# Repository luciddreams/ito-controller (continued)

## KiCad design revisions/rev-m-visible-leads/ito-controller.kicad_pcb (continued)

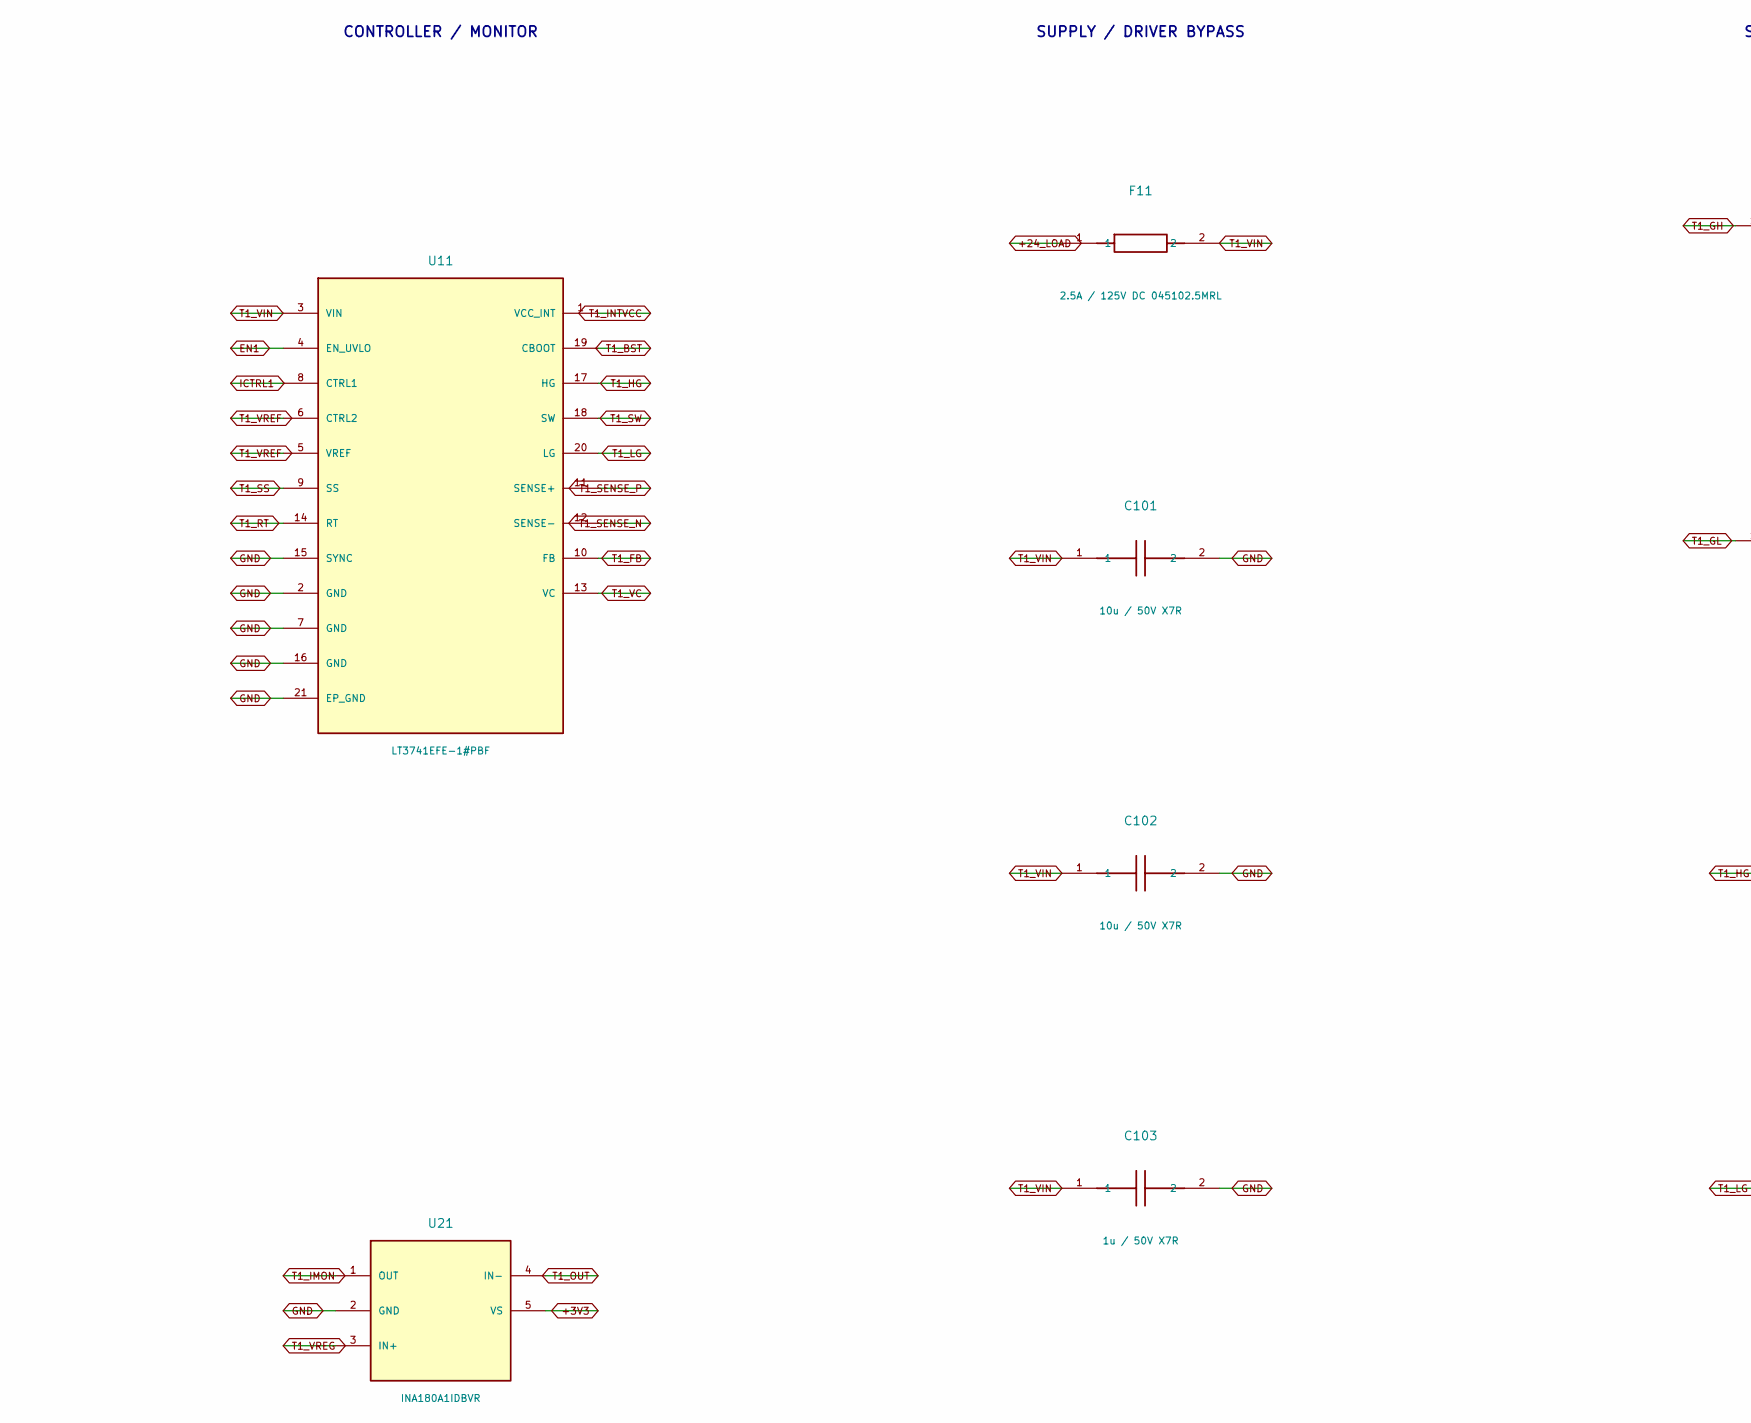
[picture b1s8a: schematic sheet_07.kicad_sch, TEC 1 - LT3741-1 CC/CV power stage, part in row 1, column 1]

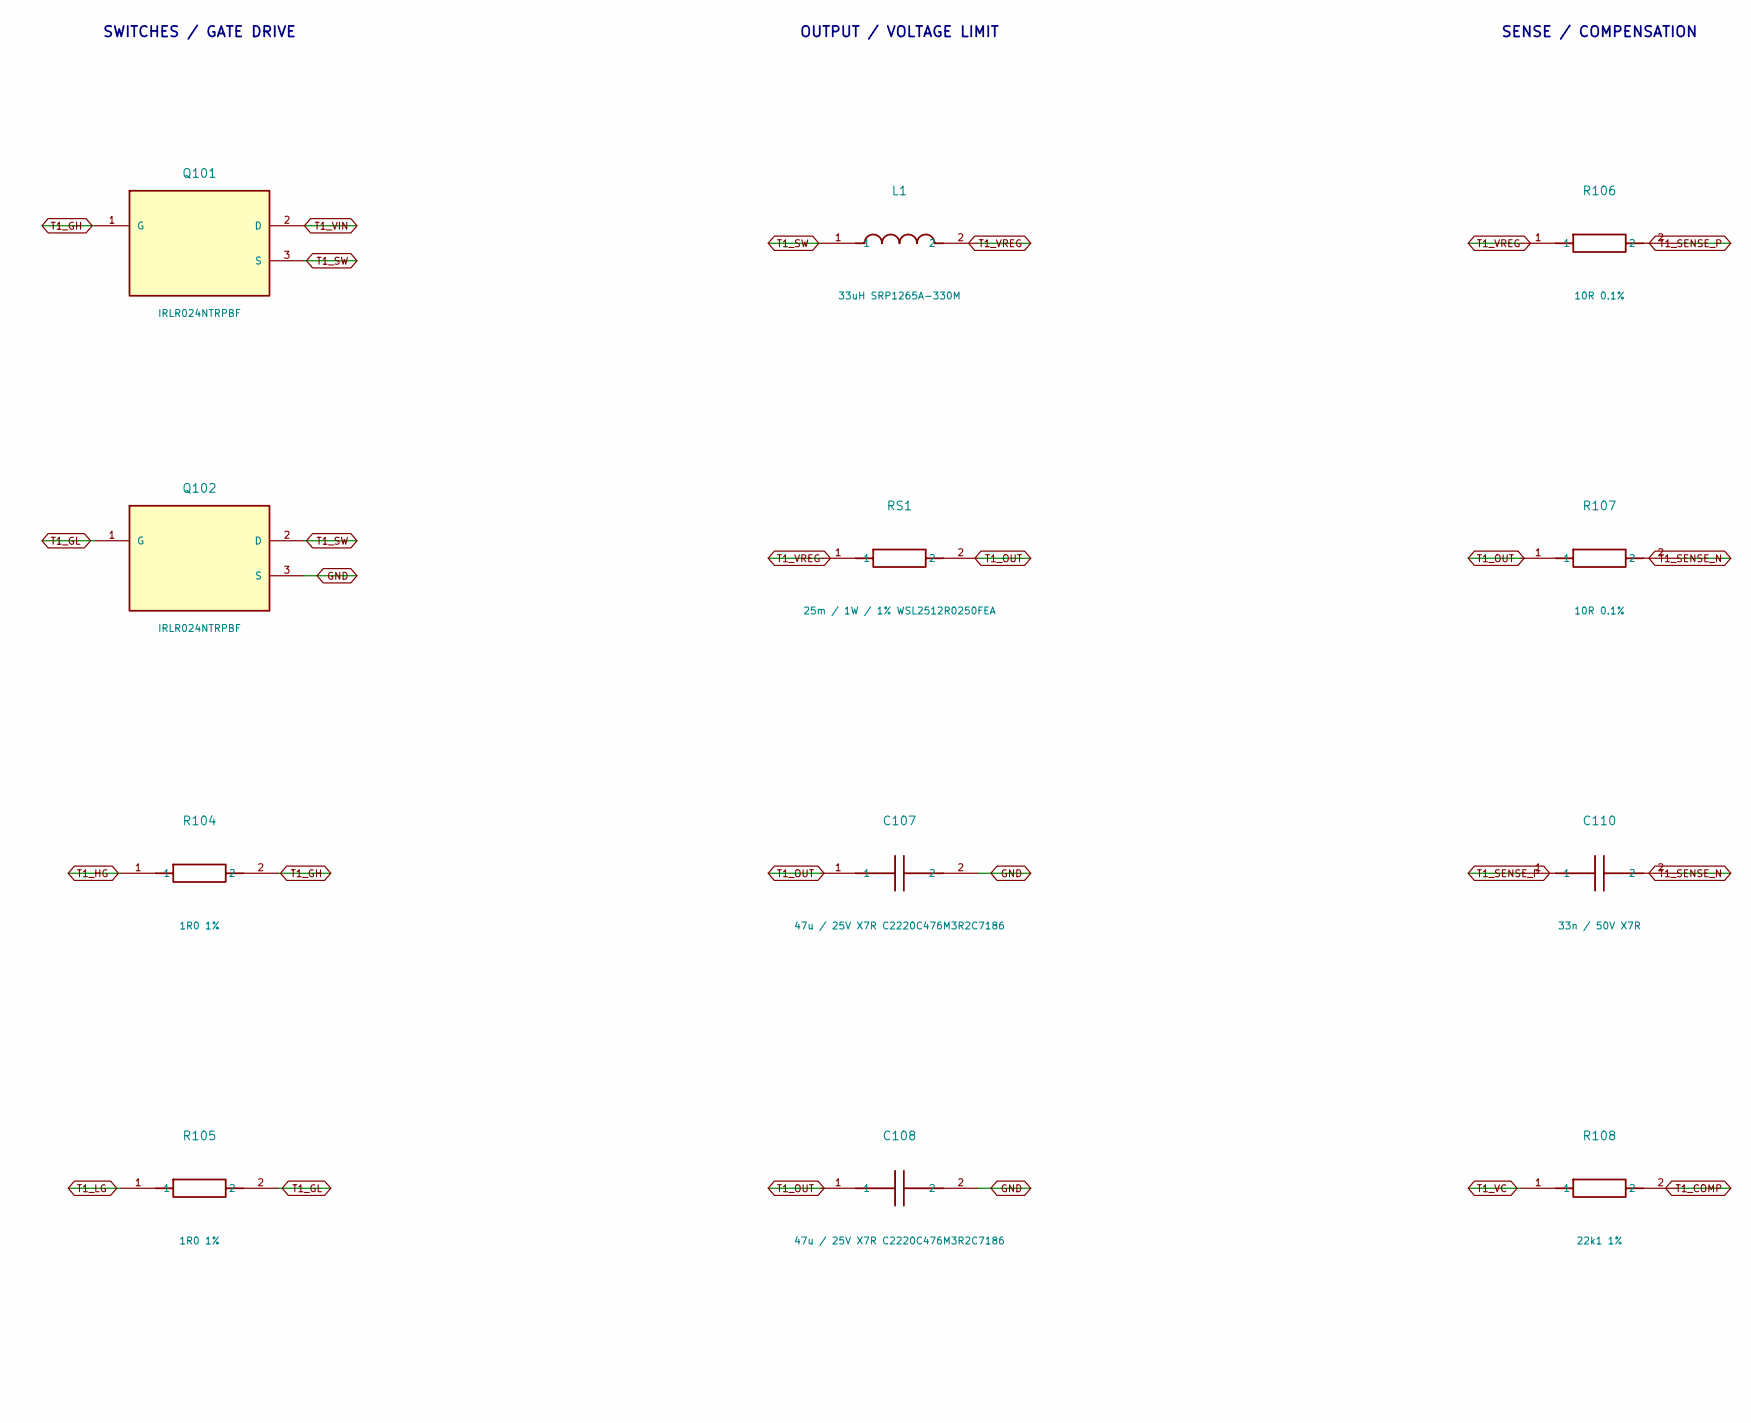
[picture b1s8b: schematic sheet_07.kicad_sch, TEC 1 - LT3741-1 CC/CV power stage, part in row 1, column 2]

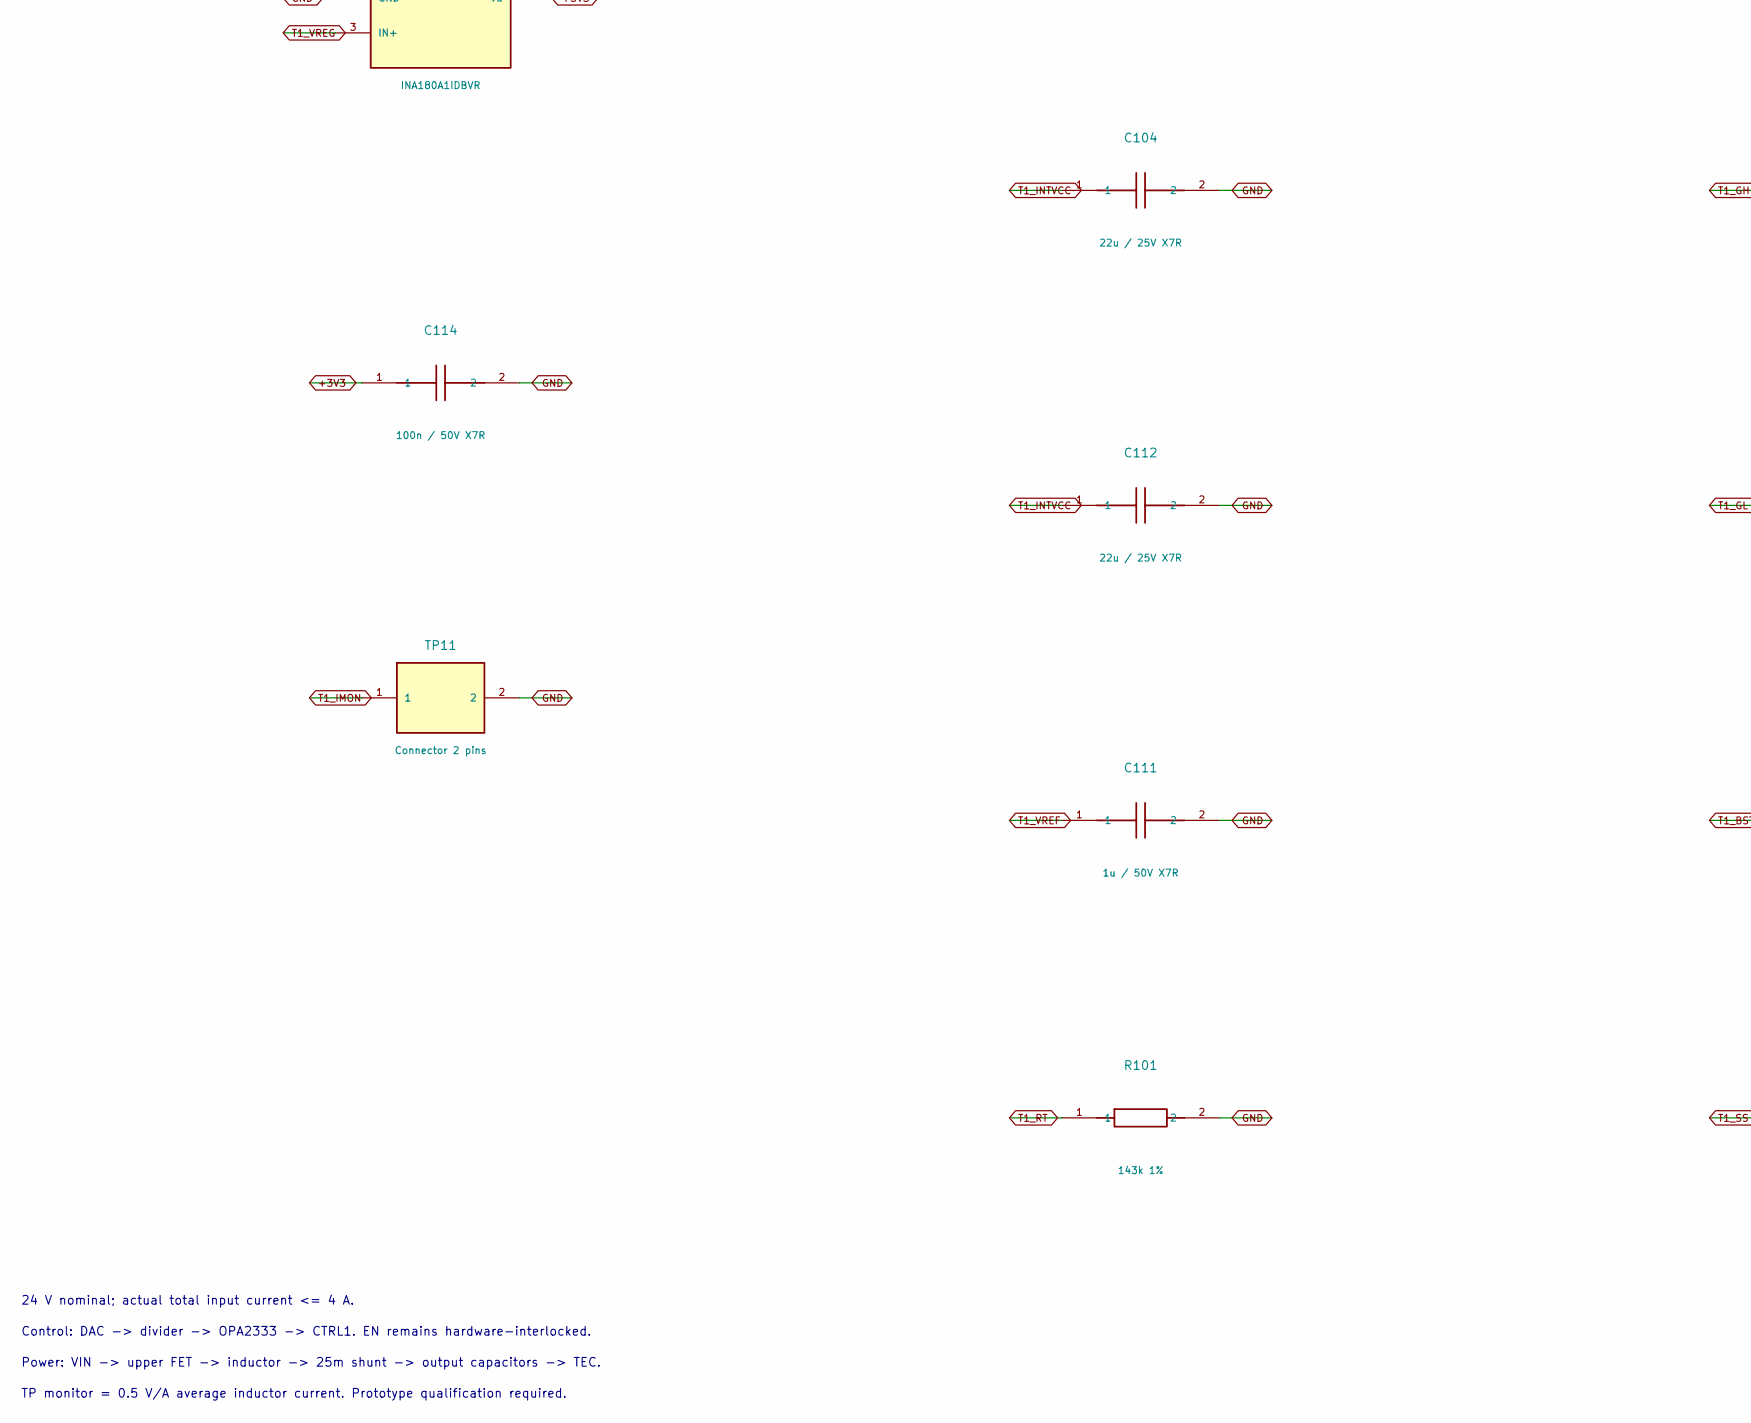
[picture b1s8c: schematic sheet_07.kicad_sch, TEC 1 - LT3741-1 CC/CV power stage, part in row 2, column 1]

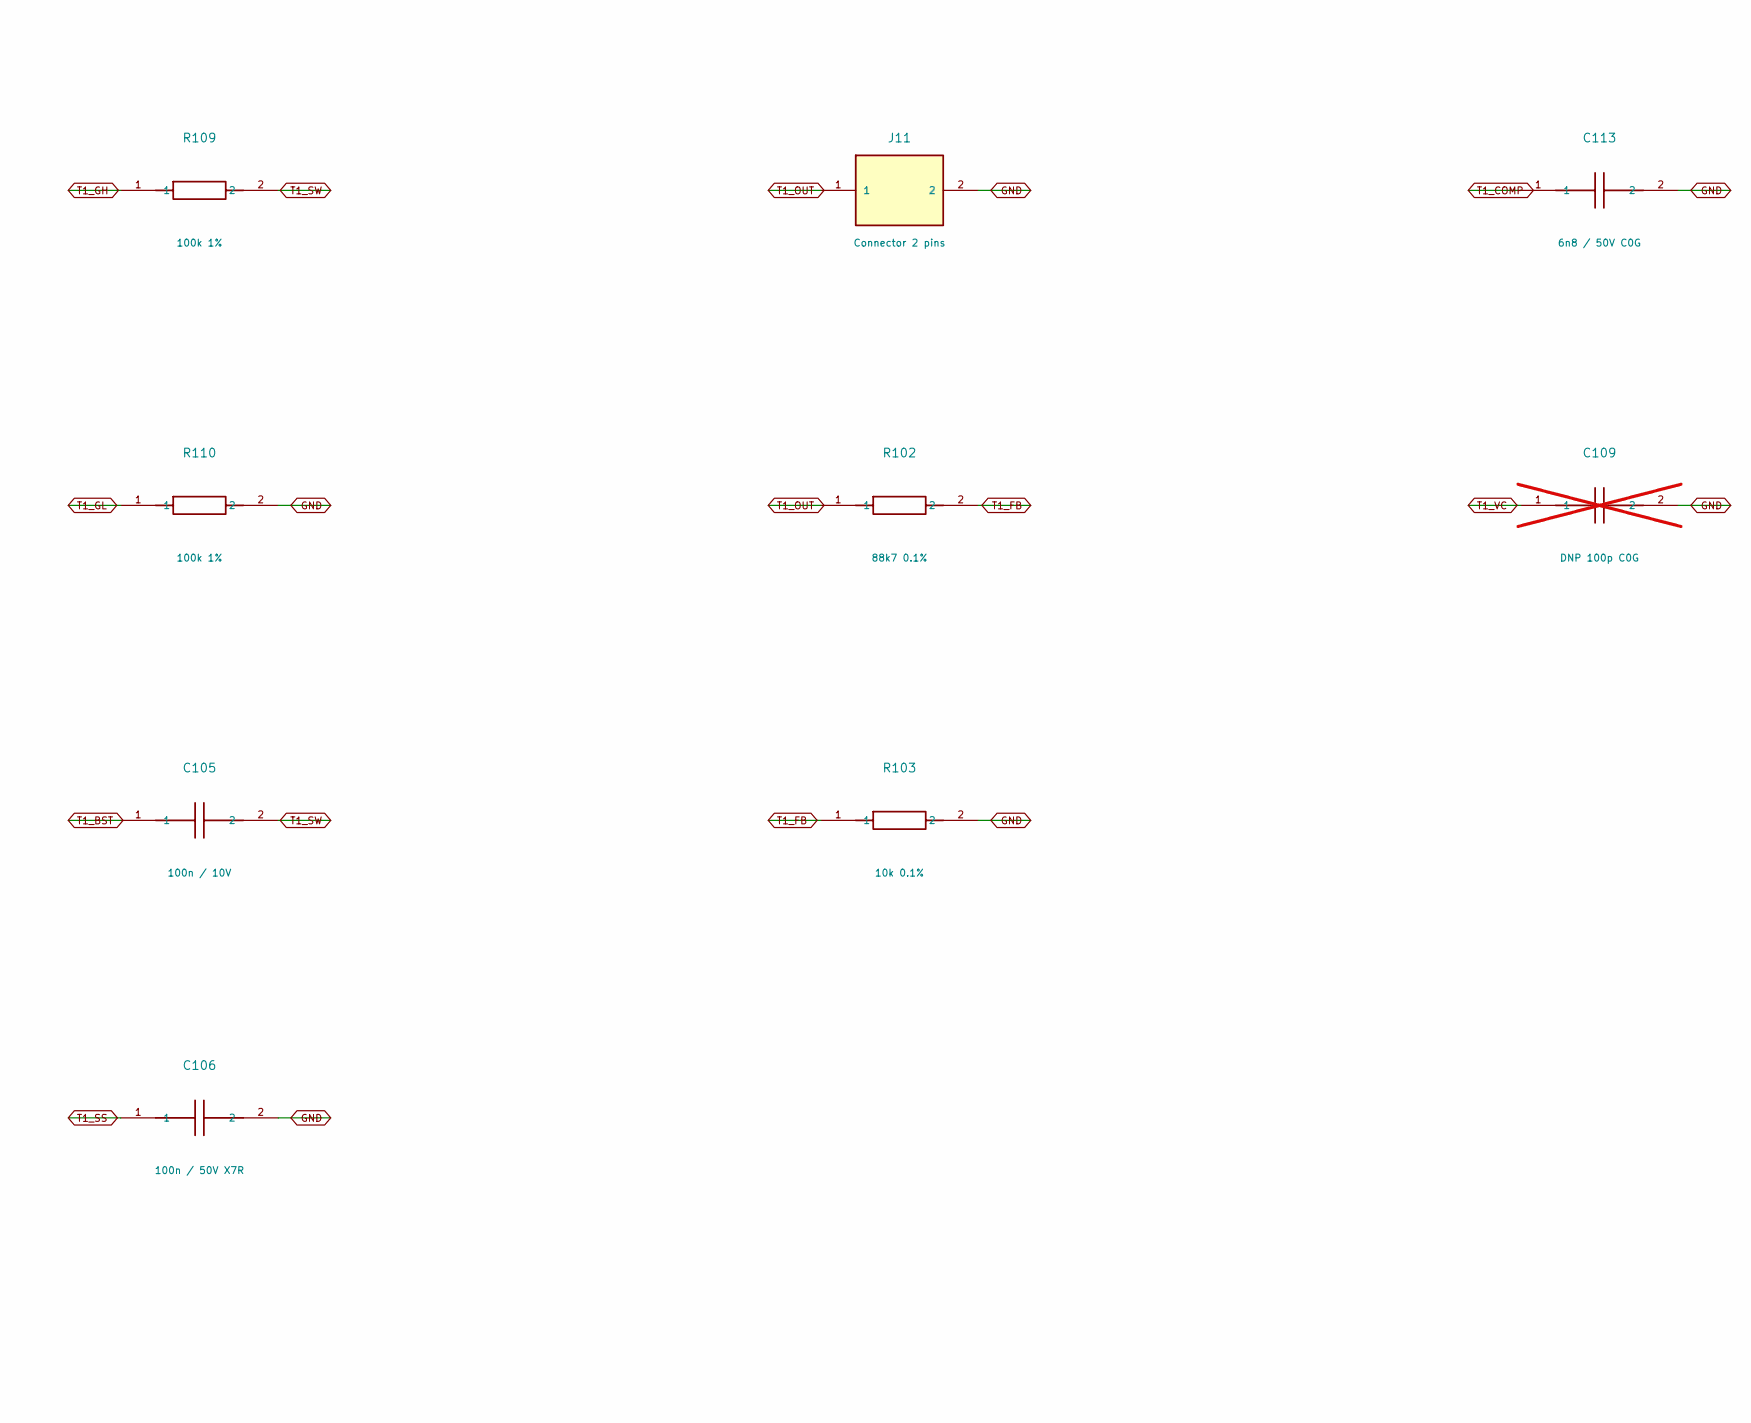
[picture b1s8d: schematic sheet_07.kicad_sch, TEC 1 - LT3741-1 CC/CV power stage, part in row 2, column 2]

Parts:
C101, C102: 10u / 50V X7R; C_1210_3225Metric; MPN GRM32ER71H106KA12L
C103, C111: 1u / 50V X7R; C_0805_2012Metric; MPN GRM21BR71H105KA12L
C104, C112: 22u / 25V X7R; C_1210_3225Metric; MPN GRM32ER71E226KE15L
C105: 100n / 10V; C_0805_2012Metric; MPN GRM21BR71H104KA01L
C106, C114: 100n / 50V X7R; C_0805_2012Metric; MPN GRM21BR71H104KA01L
C107, C108: 47u / 25V X7R C2220C476M3R2C7186; KEMET_KPS_2220_Double; MPN C2220C476M3R2C7186
C109: DNP 100p C0G; C_0805_2012Metric; MPN GRM21A5C1H101JA01D; not fitted
C110: 33n / 50V X7R; C_0805_2012Metric; MPN GRM21BR71H333KA01L
C113: 6n8 / 50V C0G; C_0805_2012Metric; MPN GRM2165C1H682JA01D
F11: 2.5A / 125V DC 045102.5MRL; Littelfuse_451; MPN 045102.5MRL
J11: Connector 2 pins; TerminalBlock_Phoenix_MKDS-1,5-2-5.08_1x02_P5.08mm_Horizont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; MPN 1715721
L1: 33uH SRP1265A-330M; Bourns_SRP1265A; MPN SRP1265A-330M
Q101, Q102: IRLR024NTRPBF; Infineon_DPAK_TO252_3; MPN IRLR024NTRPBF
R101: 143k 1%; R_0805_2012Metric; MPN RC0805FR-07143KL
R102: 88k7 0.1%; R_0805_2012Metric; MPN RT0805BRD0788K7L
R103: 10k 0.1%; R_0805_2012Metric; MPN RT0805BRD0710KL
R104, R105: 1R0 1%; R_0805_2012Metric; MPN RC0805FR-071RL
R106, R107: 10R 0.1%; R_0805_2012Metric; MPN RT0805BRD0710RL
R108: 22k1 1%; R_0805_2012Metric; MPN RC0805FR-0722K1L
R109, R110: 100k 1%; R_0805_2012Metric; MPN RC0805FR-07100KL
RS1: 25m / 1W / 1% WSL2512R0250FEA; WSL2512_7m_to_500m; MPN WSL2512R0250FEA
TP11: Connector 2 pins; PinHeader_1x02_P2.54mm_Vertical; MPN TSW-102-07-G-S
U11: LT3741EFE-1#PBF; LT_FE20_EP2.74x3.86; MPN LT3741EFE-1#PBF
U21: INA180A1IDBVR; SOT-23-5; MPN INA180A1IDBVR

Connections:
+3V3: C114.1, U21.5 (VS); also elsewhere on the board
+24_LOAD: F11.1; also elsewhere on the board
EN1: U11.4 (EN_UVLO); also elsewhere on the board
GND: C101.2, C102.2, C103.2, C104.2, C106.2, C107.2, C108.2, C109.2, C111.2, C112.2, C113.2, C114.2, J11.2, Q102.3 (S), R101.2, R103.2, R110.2, TP11.2, U11.2 (GND), U11.7 (GND), U11.15 (SYNC), U11.16 (GND), U11.21 (EP_GND), U21.2 (GND); also elsewhere on the board
ICTRL1: U11.8 (CTRL1); also elsewhere on the board
T1_BST: C105.1, U11.19 (CBOOT)
T1_COMP: C113.1, R108.2
T1_FB: R102.2, R103.1, U11.10 (FB)
T1_GH: Q101.1 (G), R104.2, R109.1
T1_GL: Q102.1 (G), R105.2, R110.1
T1_HG: R104.1, U11.17 (HG)
T1_IMON: TP11.1, U21.1 (OUT)
T1_INTVCC: C104.1, C112.1, U11.1 (VCC_INT)
T1_LG: R105.1, U11.20 (LG)
T1_OUT: C107.1, C108.1, J11.1, R102.1, R107.1, RS1.2, U21.4 (IN-)
T1_RT: R101.1, U11.14 (RT)
T1_SENSE_N: C110.2, R107.2, U11.12 (SENSE-)
T1_SENSE_P: C110.1, R106.2, U11.11 (SENSE+)
T1_SS: C106.1, U11.9 (SS)
T1_SW: C105.2, L1.1, Q101.3 (S), Q102.2 (D), R109.2, U11.18 (SW)
T1_VC: C109.1, R108.1, U11.13 (VC)
T1_VIN: C101.1, C102.1, C103.1, F11.2, Q101.2 (D), U11.3 (VIN)
T1_VREF: C111.1, U11.5 (VREF), U11.6 (CTRL2)
T1_VREG: L1.2, R106.1, RS1.1, U21.3 (IN+)

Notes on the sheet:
CONTROLLER / MONITOR
SUPPLY / DRIVER BYPASS
SWITCHES / GATE DRIVE
OUTPUT / VOLTAGE LIMIT
SENSE / COMPENSATION
24 V nominal; actual total input current <= 4 A.
Control: DAC -> divider -> OPA2333 -> CTRL1. EN remains hardware-interlocked.
Power: VIN -> upper FET -> inductor -> 25m shunt -> output capacitors -> TEC.
TP monitor = 0.5 V/A average inductor current. Prototype qualification required.

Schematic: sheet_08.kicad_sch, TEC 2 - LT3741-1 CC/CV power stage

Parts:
C201, C202: 10u / 50V X7R; C_1210_3225Metric; MPN GRM32ER71H106KA12L
C203, C211: 1u / 50V X7R; C_0805_2012Metric; MPN GRM21BR71H105KA12L
C204, C212: 22u / 25V X7R; C_1210_3225Metric; MPN GRM32ER71E226KE15L
C205: 100n / 10V; C_0805_2012Metric; MPN GRM21BR71H104KA01L
C206, C214: 100n / 50V X7R; C_0805_2012Metric; MPN GRM21BR71H104KA01L
C207, C208: 47u / 25V X7R C2220C476M3R2C7186; KEMET_KPS_2220_Double; MPN C2220C476M3R2C7186
C209: DNP 100p C0G; C_0805_2012Metric; MPN GRM21A5C1H101JA01D; not fitted
C210: 33n / 50V X7R; C_0805_2012Metric; MPN GRM21BR71H333KA01L
C213: 6n8 / 50V C0G; C_0805_2012Metric; MPN GRM2165C1H682JA01D
F12: 2.5A / 125V DC 045102.5MRL; Littelfuse_451; MPN 045102.5MRL
J12: Connector 2 pins; TerminalBlock_Phoenix_MKDS-1,5-2-5.08_1x02_P5.08mm_Horizont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; MPN 1715721
L2: 33uH SRP1265A-330M; Bourns_SRP1265A; MPN SRP1265A-330M
Q201, Q202: IRLR024NTRPBF; Infineon_DPAK_TO252_3; MPN IRLR024NTRPBF
R201: 143k 1%; R_0805_2012Metric; MPN RC0805FR-07143KL
R202: 88k7 0.1%; R_0805_2012Metric; MPN RT0805BRD0788K7L
R203: 10k 0.1%; R_0805_2012Metric; MPN RT0805BRD0710KL
R204, R205: 1R0 1%; R_0805_2012Metric; MPN RC0805FR-071RL
R206, R207: 10R 0.1%; R_0805_2012Metric; MPN RT0805BRD0710RL
R208: 22k1 1%; R_0805_2012Metric; MPN RC0805FR-0722K1L
R209, R210: 100k 1%; R_0805_2012Metric; MPN RC0805FR-07100KL
RS2: 25m / 1W / 1% WSL2512R0250FEA; WSL2512_7m_to_500m; MPN WSL2512R0250FEA
TP12: Connector 2 pins; PinHeader_1x02_P2.54mm_Vertical; MPN TSW-102-07-G-S
U12: LT3741EFE-1#PBF; LT_FE20_EP2.74x3.86; MPN LT3741EFE-1#PBF
U22: INA180A1IDBVR; SOT-23-5; MPN INA180A1IDBVR

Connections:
+3V3: C214.1, U22.5 (VS); also elsewhere on the board
+24_LOAD: F12.1; also elsewhere on the board
EN2: U12.4 (EN_UVLO); also elsewhere on the board
GND: C201.2, C202.2, C203.2, C204.2, C206.2, C207.2, C208.2, C209.2, C211.2, C212.2, C213.2, C214.2, J12.2, Q202.3 (S), R201.2, R203.2, R210.2, TP12.2, U12.2 (GND), U12.7 (GND), U12.15 (SYNC), U12.16 (GND), U12.21 (EP_GND), U22.2 (GND); also elsewhere on the board
ICTRL2: U12.8 (CTRL1); also elsewhere on the board
T2_BST: C205.1, U12.19 (CBOOT)
T2_COMP: C213.1, R208.2
T2_FB: R202.2, R203.1, U12.10 (FB)
T2_GH: Q201.1 (G), R204.2, R209.1
T2_GL: Q202.1 (G), R205.2, R210.1
T2_HG: R204.1, U12.17 (HG)
T2_IMON: TP12.1, U22.1 (OUT)
T2_INTVCC: C204.1, C212.1, U12.1 (VCC_INT)
T2_LG: R205.1, U12.20 (LG)
T2_OUT: C207.1, C208.1, J12.1, R202.1, R207.1, RS2.2, U22.4 (IN-)
T2_RT: R201.1, U12.14 (RT)
T2_SENSE_N: C210.2, R207.2, U12.12 (SENSE-)
T2_SENSE_P: C210.1, R206.2, U12.11 (SENSE+)
T2_SS: C206.1, U12.9 (SS)
T2_SW: C205.2, L2.1, Q201.3 (S), Q202.2 (D), R209.2, U12.18 (SW)
T2_VC: C209.1, R208.1, U12.13 (VC)
T2_VIN: C201.1, C202.1, C203.1, F12.2, Q201.2 (D), U12.3 (VIN)
T2_VREF: C211.1, U12.5 (VREF), U12.6 (CTRL2)
T2_VREG: L2.2, R206.1, RS2.1, U22.3 (IN+)

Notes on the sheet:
CONTROLLER / MONITOR
SUPPLY / DRIVER BYPASS
SWITCHES / GATE DRIVE
OUTPUT / VOLTAGE LIMIT
SENSE / COMPENSATION
24 V nominal; actual total input current <= 4 A.
Control: DAC -> divider -> OPA2333 -> CTRL1. EN remains hardware-interlocked.
Power: VIN -> upper FET -> inductor -> 25m shunt -> output capacitors -> TEC.
TP monitor = 0.5 V/A average inductor current. Prototype qualification required.

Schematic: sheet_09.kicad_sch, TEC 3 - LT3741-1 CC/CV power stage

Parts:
C301, C302: 10u / 50V X7R; C_1210_3225Metric; MPN GRM32ER71H106KA12L
C303, C311: 1u / 50V X7R; C_0805_2012Metric; MPN GRM21BR71H105KA12L
C304, C312: 22u / 25V X7R; C_1210_3225Metric; MPN GRM32ER71E226KE15L
C305: 100n / 10V; C_0805_2012Metric; MPN GRM21BR71H104KA01L
C306, C314: 100n / 50V X7R; C_0805_2012Metric; MPN GRM21BR71H104KA01L
C307, C308: 47u / 25V X7R C2220C476M3R2C7186; KEMET_KPS_2220_Double; MPN C2220C476M3R2C7186
C309: DNP 100p C0G; C_0805_2012Metric; MPN GRM21A5C1H101JA01D; not fitted
C310: 33n / 50V X7R; C_0805_2012Metric; MPN GRM21BR71H333KA01L
C313: 6n8 / 50V C0G; C_0805_2012Metric; MPN GRM2165C1H682JA01D
F13: 2.5A / 125V DC 045102.5MRL; Littelfuse_451; MPN 045102.5MRL
J13: Connector 2 pins; TerminalBlock_Phoenix_MKDS-1,5-2-5.08_1x02_P5.08mm_Horizont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; MPN 1715721
L3: 33uH SRP1265A-330M; Bourns_SRP1265A; MPN SRP1265A-330M
Q301, Q302: IRLR024NTRPBF; Infineon_DPAK_TO252_3; MPN IRLR024NTRPBF
R301: 143k 1%; R_0805_2012Metric; MPN RC0805FR-07143KL
R302: 88k7 0.1%; R_0805_2012Metric; MPN RT0805BRD0788K7L
R303: 10k 0.1%; R_0805_2012Metric; MPN RT0805BRD0710KL
R304, R305: 1R0 1%; R_0805_2012Metric; MPN RC0805FR-071RL
R306, R307: 10R 0.1%; R_0805_2012Metric; MPN RT0805BRD0710RL
R308: 22k1 1%; R_0805_2012Metric; MPN RC0805FR-0722K1L
R309, R310: 100k 1%; R_0805_2012Metric; MPN RC0805FR-07100KL
RS3: 25m / 1W / 1% WSL2512R0250FEA; WSL2512_7m_to_500m; MPN WSL2512R0250FEA
TP13: Connector 2 pins; PinHeader_1x02_P2.54mm_Vertical; MPN TSW-102-07-G-S
U13: LT3741EFE-1#PBF; LT_FE20_EP2.74x3.86; MPN LT3741EFE-1#PBF
U23: INA180A1IDBVR; SOT-23-5; MPN INA180A1IDBVR

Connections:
+3V3: C314.1, U23.5 (VS); also elsewhere on the board
+24_LOAD: F13.1; also elsewhere on the board
EN3: U13.4 (EN_UVLO); also elsewhere on the board
GND: C301.2, C302.2, C303.2, C304.2, C306.2, C307.2, C308.2, C309.2, C311.2, C312.2, C313.2, C314.2, J13.2, Q302.3 (S), R301.2, R303.2, R310.2, TP13.2, U13.2 (GND), U13.7 (GND), U13.15 (SYNC), U13.16 (GND), U13.21 (EP_GND), U23.2 (GND); also elsewhere on the board
ICTRL3: U13.8 (CTRL1); also elsewhere on the board
T3_BST: C305.1, U13.19 (CBOOT)
T3_COMP: C313.1, R308.2
T3_FB: R302.2, R303.1, U13.10 (FB)
T3_GH: Q301.1 (G), R304.2, R309.1
T3_GL: Q302.1 (G), R305.2, R310.1
T3_HG: R304.1, U13.17 (HG)
T3_IMON: TP13.1, U23.1 (OUT)
T3_INTVCC: C304.1, C312.1, U13.1 (VCC_INT)
T3_LG: R305.1, U13.20 (LG)
T3_OUT: C307.1, C308.1, J13.1, R302.1, R307.1, RS3.2, U23.4 (IN-)
T3_RT: R301.1, U13.14 (RT)
T3_SENSE_N: C310.2, R307.2, U13.12 (SENSE-)
T3_SENSE_P: C310.1, R306.2, U13.11 (SENSE+)
T3_SS: C306.1, U13.9 (SS)
T3_SW: C305.2, L3.1, Q301.3 (S), Q302.2 (D), R309.2, U13.18 (SW)
T3_VC: C309.1, R308.1, U13.13 (VC)
T3_VIN: C301.1, C302.1, C303.1, F13.2, Q301.2 (D), U13.3 (VIN)
T3_VREF: C311.1, U13.5 (VREF), U13.6 (CTRL2)
T3_VREG: L3.2, R306.1, RS3.1, U23.3 (IN+)

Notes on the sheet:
CONTROLLER / MONITOR
SUPPLY / DRIVER BYPASS
SWITCHES / GATE DRIVE
OUTPUT / VOLTAGE LIMIT
SENSE / COMPENSATION
24 V nominal; actual total input current <= 4 A.
Control: DAC -> divider -> OPA2333 -> CTRL1. EN remains hardware-interlocked.
Power: VIN -> upper FET -> inductor -> 25m shunt -> output capacitors -> TEC.
TP monitor = 0.5 V/A average inductor current. Prototype qualification required.

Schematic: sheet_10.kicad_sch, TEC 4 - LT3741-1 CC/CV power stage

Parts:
C401, C402: 10u / 50V X7R; C_1210_3225Metric; MPN GRM32ER71H106KA12L
C403, C411: 1u / 50V X7R; C_0805_2012Metric; MPN GRM21BR71H105KA12L
C404, C412: 22u / 25V X7R; C_1210_3225Metric; MPN GRM32ER71E226KE15L
C405: 100n / 10V; C_0805_2012Metric; MPN GRM21BR71H104KA01L
C406, C414: 100n / 50V X7R; C_0805_2012Metric; MPN GRM21BR71H104KA01L
C407, C408: 47u / 25V X7R C2220C476M3R2C7186; KEMET_KPS_2220_Double; MPN C2220C476M3R2C7186
C409: DNP 100p C0G; C_0805_2012Metric; MPN GRM21A5C1H101JA01D; not fitted
C410: 33n / 50V X7R; C_0805_2012Metric; MPN GRM21BR71H333KA01L
C413: 6n8 / 50V C0G; C_0805_2012Metric; MPN GRM2165C1H682JA01D
F14: 2.5A / 125V DC 045102.5MRL; Littelfuse_451; MPN 045102.5MRL
J14: Connector 2 pins; TerminalBlock_Phoenix_MKDS-1,5-2-5.08_1x02_P5.08mm_Horizont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; MPN 1715721
L4: 33uH SRP1265A-330M; Bourns_SRP1265A; MPN SRP1265A-330M
Q401, Q402: IRLR024NTRPBF; Infineon_DPAK_TO252_3; MPN IRLR024NTRPBF
R401: 143k 1%; R_0805_2012Metric; MPN RC0805FR-07143KL
R402: 88k7 0.1%; R_0805_2012Metric; MPN RT0805BRD0788K7L
R403: 10k 0.1%; R_0805_2012Metric; MPN RT0805BRD0710KL
R404, R405: 1R0 1%; R_0805_2012Metric; MPN RC0805FR-071RL
R406, R407: 10R 0.1%; R_0805_2012Metric; MPN RT0805BRD0710RL
R408: 22k1 1%; R_0805_2012Metric; MPN RC0805FR-0722K1L
R409, R410: 100k 1%; R_0805_2012Metric; MPN RC0805FR-07100KL
RS4: 25m / 1W / 1% WSL2512R0250FEA; WSL2512_7m_to_500m; MPN WSL2512R0250FEA
TP14: Connector 2 pins; PinHeader_1x02_P2.54mm_Vertical; MPN TSW-102-07-G-S
U14: LT3741EFE-1#PBF; LT_FE20_EP2.74x3.86; MPN LT3741EFE-1#PBF
U24: INA180A1IDBVR; SOT-23-5; MPN INA180A1IDBVR

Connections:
+3V3: C414.1, U24.5 (VS); also elsewhere on the board
+24_LOAD: F14.1; also elsewhere on the board
EN4: U14.4 (EN_UVLO); also elsewhere on the board
GND: C401.2, C402.2, C403.2, C404.2, C406.2, C407.2, C408.2, C409.2, C411.2, C412.2, C413.2, C414.2, J14.2, Q402.3 (S), R401.2, R403.2, R410.2, TP14.2, U14.2 (GND), U14.7 (GND), U14.15 (SYNC), U14.16 (GND), U14.21 (EP_GND), U24.2 (GND); also elsewhere on the board
ICTRL4: U14.8 (CTRL1); also elsewhere on the board
T4_BST: C405.1, U14.19 (CBOOT)
T4_COMP: C413.1, R408.2
T4_FB: R402.2, R403.1, U14.10 (FB)
T4_GH: Q401.1 (G), R404.2, R409.1
T4_GL: Q402.1 (G), R405.2, R410.1
T4_HG: R404.1, U14.17 (HG)
T4_IMON: TP14.1, U24.1 (OUT)
T4_INTVCC: C404.1, C412.1, U14.1 (VCC_INT)
T4_LG: R405.1, U14.20 (LG)
T4_OUT: C407.1, C408.1, J14.1, R402.1, R407.1, RS4.2, U24.4 (IN-)
T4_RT: R401.1, U14.14 (RT)
T4_SENSE_N: C410.2, R407.2, U14.12 (SENSE-)
T4_SENSE_P: C410.1, R406.2, U14.11 (SENSE+)
T4_SS: C406.1, U14.9 (SS)
T4_SW: C405.2, L4.1, Q401.3 (S), Q402.2 (D), R409.2, U14.18 (SW)
T4_VC: C409.1, R408.1, U14.13 (VC)
T4_VIN: C401.1, C402.1, C403.1, F14.2, Q401.2 (D), U14.3 (VIN)
T4_VREF: C411.1, U14.5 (VREF), U14.6 (CTRL2)
T4_VREG: L4.2, R406.1, RS4.1, U24.3 (IN+)

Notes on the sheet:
CONTROLLER / MONITOR
SUPPLY / DRIVER BYPASS
SWITCHES / GATE DRIVE
OUTPUT / VOLTAGE LIMIT
SENSE / COMPENSATION
24 V nominal; actual total input current <= 4 A.
Control: DAC -> divider -> OPA2333 -> CTRL1. EN remains hardware-interlocked.
Power: VIN -> upper FET -> inductor -> 25m shunt -> output capacitors -> TEC.
TP monitor = 0.5 V/A average inductor current. Prototype qualification required.

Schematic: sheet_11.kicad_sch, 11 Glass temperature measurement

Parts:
C40, C41, C42, C43, C44: 100n / 10V; C_0805_2012Metric; MPN GRM21BR71H104KA01L
J21, J22, J23, J24: Connector 2 pins; JST_XH_B2B-XH-A_1x02_P2.50mm_Vertical; MPN B2B-XH-A(LF)(SN)
R61, R62, R63, R64: 10k 0.1%; R_0805_2012Metric; MPN RT0805BRD0710KL
R65, R66, R67, R68: 1k; R_0805_2012Metric; MPN RC0805FR-071KL
U9: ADS1115IDGS; VSSOP-10_3x3mm_P0.5mm; MPN ADS1115IDGSR

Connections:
+3V3: C40.1, R61.1, R62.1, R63.1, R64.1, U9.8 (VDD); also elsewhere on the board
GND: C40.2, C41.2, C42.2, C43.2, C44.2, J21.2, J22.2, J23.2, J24.2, U9.1 (ADDR), U9.3 (GND); also elsewhere on the board
NTC1: J21.1, R61.2, R65.1
NTC2: J22.1, R62.2, R66.1
NTC3: J23.1, R63.2, R67.1
NTC4: J24.1, R64.2, R68.1
SCL: U9.10 (SCL); also elsewhere on the board
SDA: U9.9 (SDA); also elsewhere on the board
TEMP_ADC1: C41.1, R65.2, U9.4 (AIN0)
TEMP_ADC2: C42.1, R66.2, U9.5 (AIN1)
TEMP_ADC3: C43.1, R67.2, U9.6 (AIN2)
TEMP_ADC4: C44.1, R68.2, U9.7 (AIN3)

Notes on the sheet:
+3V3
11 Glass temperature measurement
ITO controller L | 24 V | prototype 4 A | wiring matches existing PCB

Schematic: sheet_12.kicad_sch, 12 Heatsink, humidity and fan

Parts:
C50: 100n / 10V; C_0805_2012Metric; MPN GRM21BR71H104KA01L
F3: 1A / 125V DC 0451001.MRL; Littelfuse_451; MPN 0451001.MRL
J25: Connector 2 pins; JST_XH_B2B-XH-A_1x02_P2.50mm_Vertical; MPN B2B-XH-A(LF)(SN)
J26, J27: Connector 4 pins; JST_XH_B4B-XH-A_1x04_P2.50mm_Vertical; MPN B4B-XH-A(LF)(SN)
Q6: MMBT3904; SOT-23; MPN MMBT3904LT1G
R70: 10k 0.1%; R_0805_2012Metric; MPN RT0805BRD0710KL
R71: 1k; R_0805_2012Metric; MPN RC0805FR-071KL
R72: 4k7; R_0805_2012Metric; MPN RC0805FR-074K7L
R73: 100k; R_0805_2012Metric; MPN RC0805FR-07100KL
R74: 10k; R_0805_2012Metric; MPN RC0805FR-0710KL

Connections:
+3V3: J26.1, R70.1, R74.1; also elsewhere on the board
+24_PROT: F3.1; also elsewhere on the board
FAN_24: F3.2, J27.2
FAN_BASE: Q6.1, R72.2, R73.1
FAN_PWM: R72.1; also elsewhere on the board
FAN_PWM_OC: J27.4, Q6.3
FAN_TACH: J27.3, R74.2; also elsewhere on the board
GND: C50.2, J25.2, J26.2, J27.1, Q6.2, R73.2; also elsewhere on the board
HOT_ADC: C50.1, R71.2; also elsewhere on the board
HOT_NTC: J25.1, R70.2, R71.1
SCL: J26.4; also elsewhere on the board
SDA: J26.3; also elsewhere on the board

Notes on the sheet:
+3V3
+24_PROT
12 Heatsink, humidity and fan
ITO controller L | 24 V | prototype 4 A | wiring matches existing PCB

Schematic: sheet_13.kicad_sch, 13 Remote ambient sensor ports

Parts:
C51, C52: 1u / 50V X7R; C_0805_2012Metric
F4, F5: 250mA / 125V 0451.250MRL; Littelfuse_451
J28: AMBIENT 1 - LOCAL ADAPTER; JST_XH_B5B-XH-A_1x05_P2.50mm_Vertical
J29: AMBIENT 2 - LOCAL ADAPTER; JST_XH_B5B-XH-A_1x05_P2.50mm_Vertical

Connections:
+3V3: J28.1 (3V3REF), J29.1 (3V3REF); also elsewhere on the board
+5_AMB1: C51.1, F4.2, J28.5 (5V)
+5_AMB2: C52.1, F5.2, J29.5 (5V)
+5_AUX: F4.1, F5.1; also elsewhere on the board
GND: C51.2, C52.2, J28.2 (GND), J29.2 (GND); also elsewhere on the board
SCL: J28.4 (SCL), J29.4 (SCL); also elsewhere on the board
SDA: J28.3 (SDA), J29.3 (SDA); also elsewhere on the board

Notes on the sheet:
+3V3
+5_AUX
13 Remote ambient sensor ports
ITO controller L | 24 V | prototype 4 A | wiring matches existing PCB
